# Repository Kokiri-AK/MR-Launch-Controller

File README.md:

# MR-Launch-Controller
Model Rocket Launch Controller Schematic

Original Schematic: Ryan Wilkus

Forked by Jonathan M

Circuit is originally based on a great paper from 2009 by J.R. Brohm discussing model rocket igniter continuity testing [Paper](https://www.rocketshoppe.com/info/Igniter_Continuity_Tests.pdf). 

The paper proposed using a transistor circuit to decrease the continuity check current of the igniter. This circuit is an expanded realization of that suggestion.

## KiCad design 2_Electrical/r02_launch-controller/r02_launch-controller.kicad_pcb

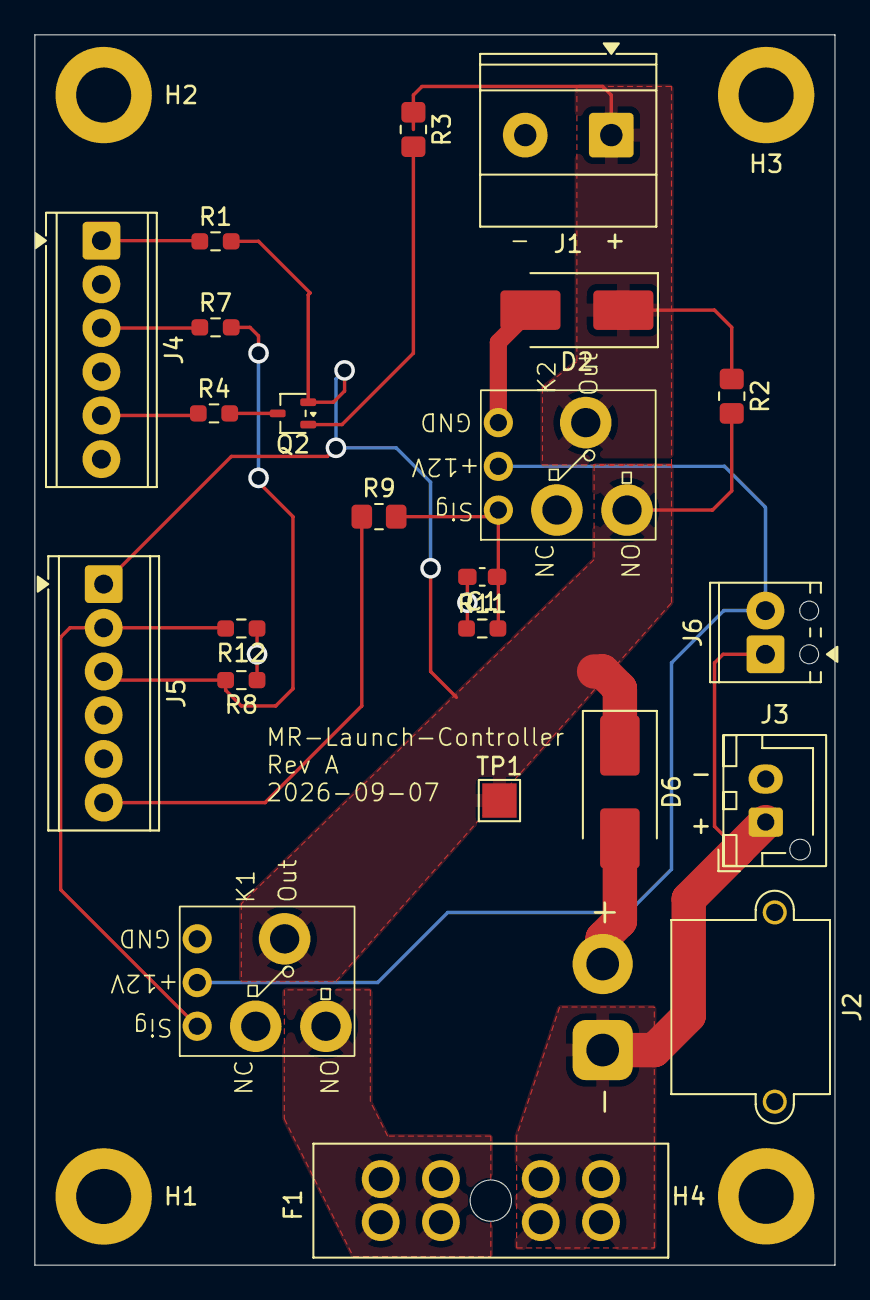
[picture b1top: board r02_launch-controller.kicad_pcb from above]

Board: 2 copper layers, 46.5 x 71.5 mm, 27 parts (0 on the bottom side), 15 nets.

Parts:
C1: .1uf; C_0603_1608Metric_Pad1.08x0.95mm_HandSolder
D2, D6: SM6T18A; D_SMB_Handsoldering
F1: 178.6165.0001; FuseHolder_Blade_ATO_Littelfuse_FLR_178.6165
H1, H2, H3, H4: MountingHole; MountingHole_3.2mm_M3_DIN965_Pad
J1: 1729128; TerminalBlock_Phoenix_MKDS-1,5-2_1x02_P5.00mm_Horizontal
J2: XT30PW-M; AMASS_XT30PW-M_1x02_P2.50mm_Horizontal
J3: B2B-XH-AM; JST_XH_B2B-XH-AM_1x02_P2.50mm_Vertical
J4, J5: 1725698; TerminalBlock_Phoenix_MPT-0,5-6-2.54_1x06_P2.54mm_Horizontal
J6: Screw_Terminal_01x02; TerminalBlock_Phoenix_MPT-0,5-2-2.54_1x02_P2.54mm_Horizontal
K1, K2: 12V-relay
Q2: BC807W; SOT-323_SC-70
R1, R4, R7: 300; R_0603_1608Metric_Pad0.98x0.95mm_HandSolder
R2, R3: 4.7K; R_0805_2012Metric_Pad1.20x1.40mm_HandSolder
R8, R11, R12: 10K; R_0603_1608Metric_Pad0.98x0.95mm_HandSolder
R9: 60; R_0805_2012Metric_Pad1.20x1.40mm_HandSolder
TP1: TestPoint; TestPoint_Pad_2.0x2.0mm

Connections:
+12V: J6.2, K1.2 (+12V), K2.2 (+12V)
/armed: J5.3, J5.4, J5.5, R7.2, R8.2
/armed_LED: J4.3, R7.1
/battery: F1.1, J2.1, J3.1, J6.1
/continuity_LED: J4.5, R4.1
/igniter_hot: D2.1, J1.1, K2.6 (OUT), R2.1, R3.1
/launch: J5.6, R9.1
/launch_sw: C1.1, K2.1 (Signal), R9.2, R11.2
/power_LED: J4.1, R1.1
/safe_relay: J5.2, K1.1 (Signal), R12.2
/safed_power: D6.1, J5.1, K1.6 (OUT), K2.4 (NO), Q2.2 (E), R1.2, R2.2, TP1.1 (1_1)
GND: C1.2, D2.2, D6.2, J1.2, J2.2, J3.2, J4.2, J4.4, J4.6, K1.3 (GND), K1.5 (NC), K2.3 (GND), K2.5 (NC), R8.1, R11.1, R12.1
unnamed: F1.2, K1.4 (NO)
unnamed: Q2.1 (B), R3.2
unnamed: Q2.3 (C), R4.2

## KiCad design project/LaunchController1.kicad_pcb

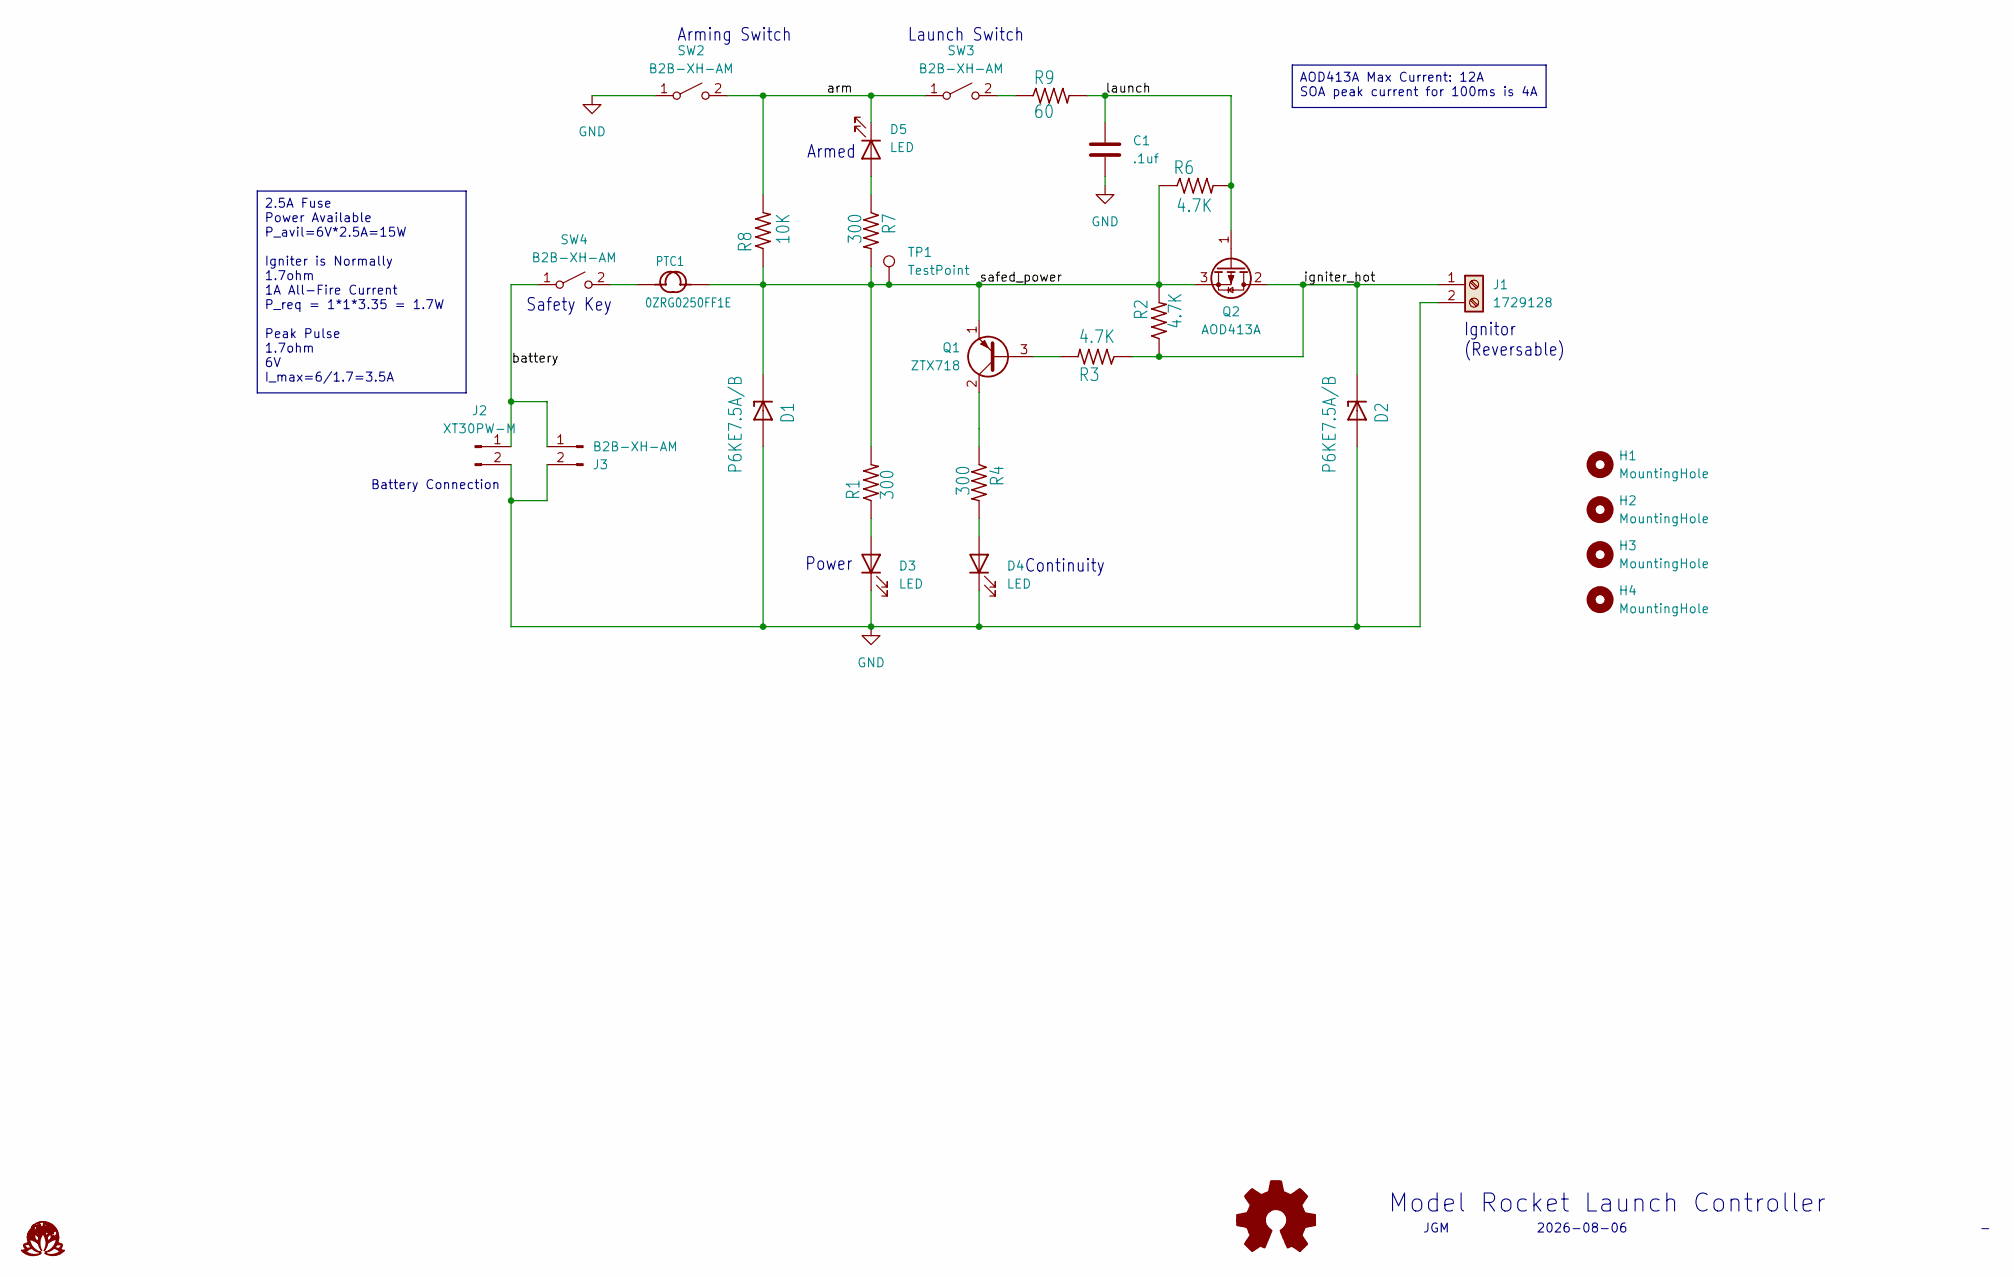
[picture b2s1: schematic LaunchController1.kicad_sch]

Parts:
C1: .1uf; C_0603_1608Metric_Pad1.08x0.95mm_HandSolder
D1, D2: P6KE7.5A/B; D_DO-15_P12.70mm_Horizontal
D3, D4, D5: LED; LED_D5.0mm
H1, H2, H3, H4: MountingHole; MountingHole_3.2mm_M3_DIN965_Pad
J1: 1729128; TerminalBlock_Phoenix_MKDS-1,5-2_1x02_P5.00mm_Horizontal
J2: XT30PW-M; AMASS_XT30PW-M_1x02_P2.50mm_Horizontal
J3: B2B-XH-AM; JST_XH_B2B-XH-AM_1x02_P2.50mm_Vertical
PTC1: 0ZRG0250FF1E; Fuse_BelFuse_0ZRE0012FF_L8.3mm_W3.8mm
Q1: ZTX718; TO-92_Inline
Q2: AOD413A; TO-252-3_TabPin2
R1, R4, R7: 300; R_Axial_DIN0309_L9.0mm_D3.2mm_P12.70mm_Horizontal
R2, R3, R6: 4.7K; R_Axial_DIN0309_L9.0mm_D3.2mm_P12.70mm_Horizontal
R8: 10K; R_Axial_DIN0309_L9.0mm_D3.2mm_P12.70mm_Horizontal
R9: 60; R_Axial_DIN0309_L9.0mm_D3.2mm_P12.70mm_Horizontal
SW2, SW3, SW4: B2B-XH-AM; JST_XH_B2B-XH-AM_1x02_P2.50mm_Vertical
TP1: TestPoint; TestPoint_Pad_2.0x2.0mm

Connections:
/arm: D5.1 (K), R8.2, SW2.2 (B), SW3.1 (A)
/battery: J2.1, J3.1, SW4.1 (A)
/igniter_hot: D2.1, J1.1, Q2.2 (D), R2.1, R3.1
/launch: C1.1, Q2.1 (G), R6.2, R9.2
/safed_power: D1.1, PTC1.2, Q1.1 (E), Q2.3 (S), R1.2, R2.2, R6.1, R7.2, R8.1, TP1.1 (1_1)
GND: C1.2, D1.2, D2.2, D3.1 (K), D4.1 (K), J1.2, J2.2, J3.2, SW2.1 (A)
unnamed: D3.2 (A), R1.1
unnamed: D4.2 (A), R4.2
unnamed: D5.2 (A), R7.1
unnamed: Q1.3 (B), R3.2
unnamed: Q1.2 (C), R4.1
unnamed: R9.1, SW3.2 (B)
unnamed: PTC1.1, SW4.2 (B)

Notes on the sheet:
Ignitor (Reversable)
Continuity
Battery Connection
Armed
Power
Arming Switch
JGM
${COMPANY}
${REVISION}
Model Rocket Launch Controller
Launch Switch
Safety Key
2026-08-06
2.5A Fuse Power Available P_avil=6V*2.5A=15W Igniter is Normally 1.7ohm 1A All-Fire Current P_req = 1*1*3.35 = 1.7W Peak Pulse 1.7ohm 6V I_max=6/1.7=3.5A
AOD413A Max Current: 12A SOA peak current for 100ms is 4A

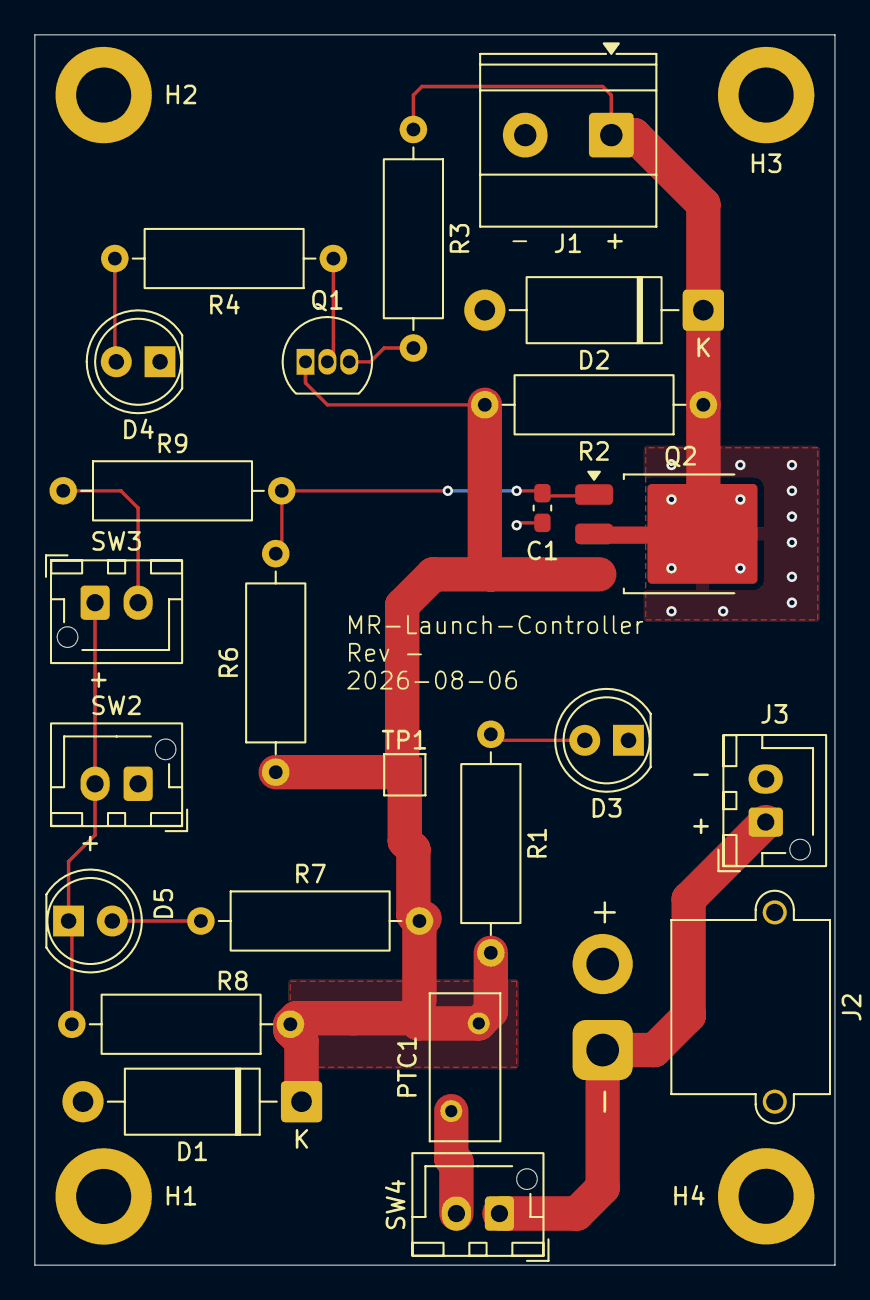
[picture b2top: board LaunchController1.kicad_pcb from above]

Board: 2 copper layers, 46.5 x 71.5 mm, 28 parts (0 on the bottom side), 13 nets.

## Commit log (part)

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2025-11-20 Created using Colab
